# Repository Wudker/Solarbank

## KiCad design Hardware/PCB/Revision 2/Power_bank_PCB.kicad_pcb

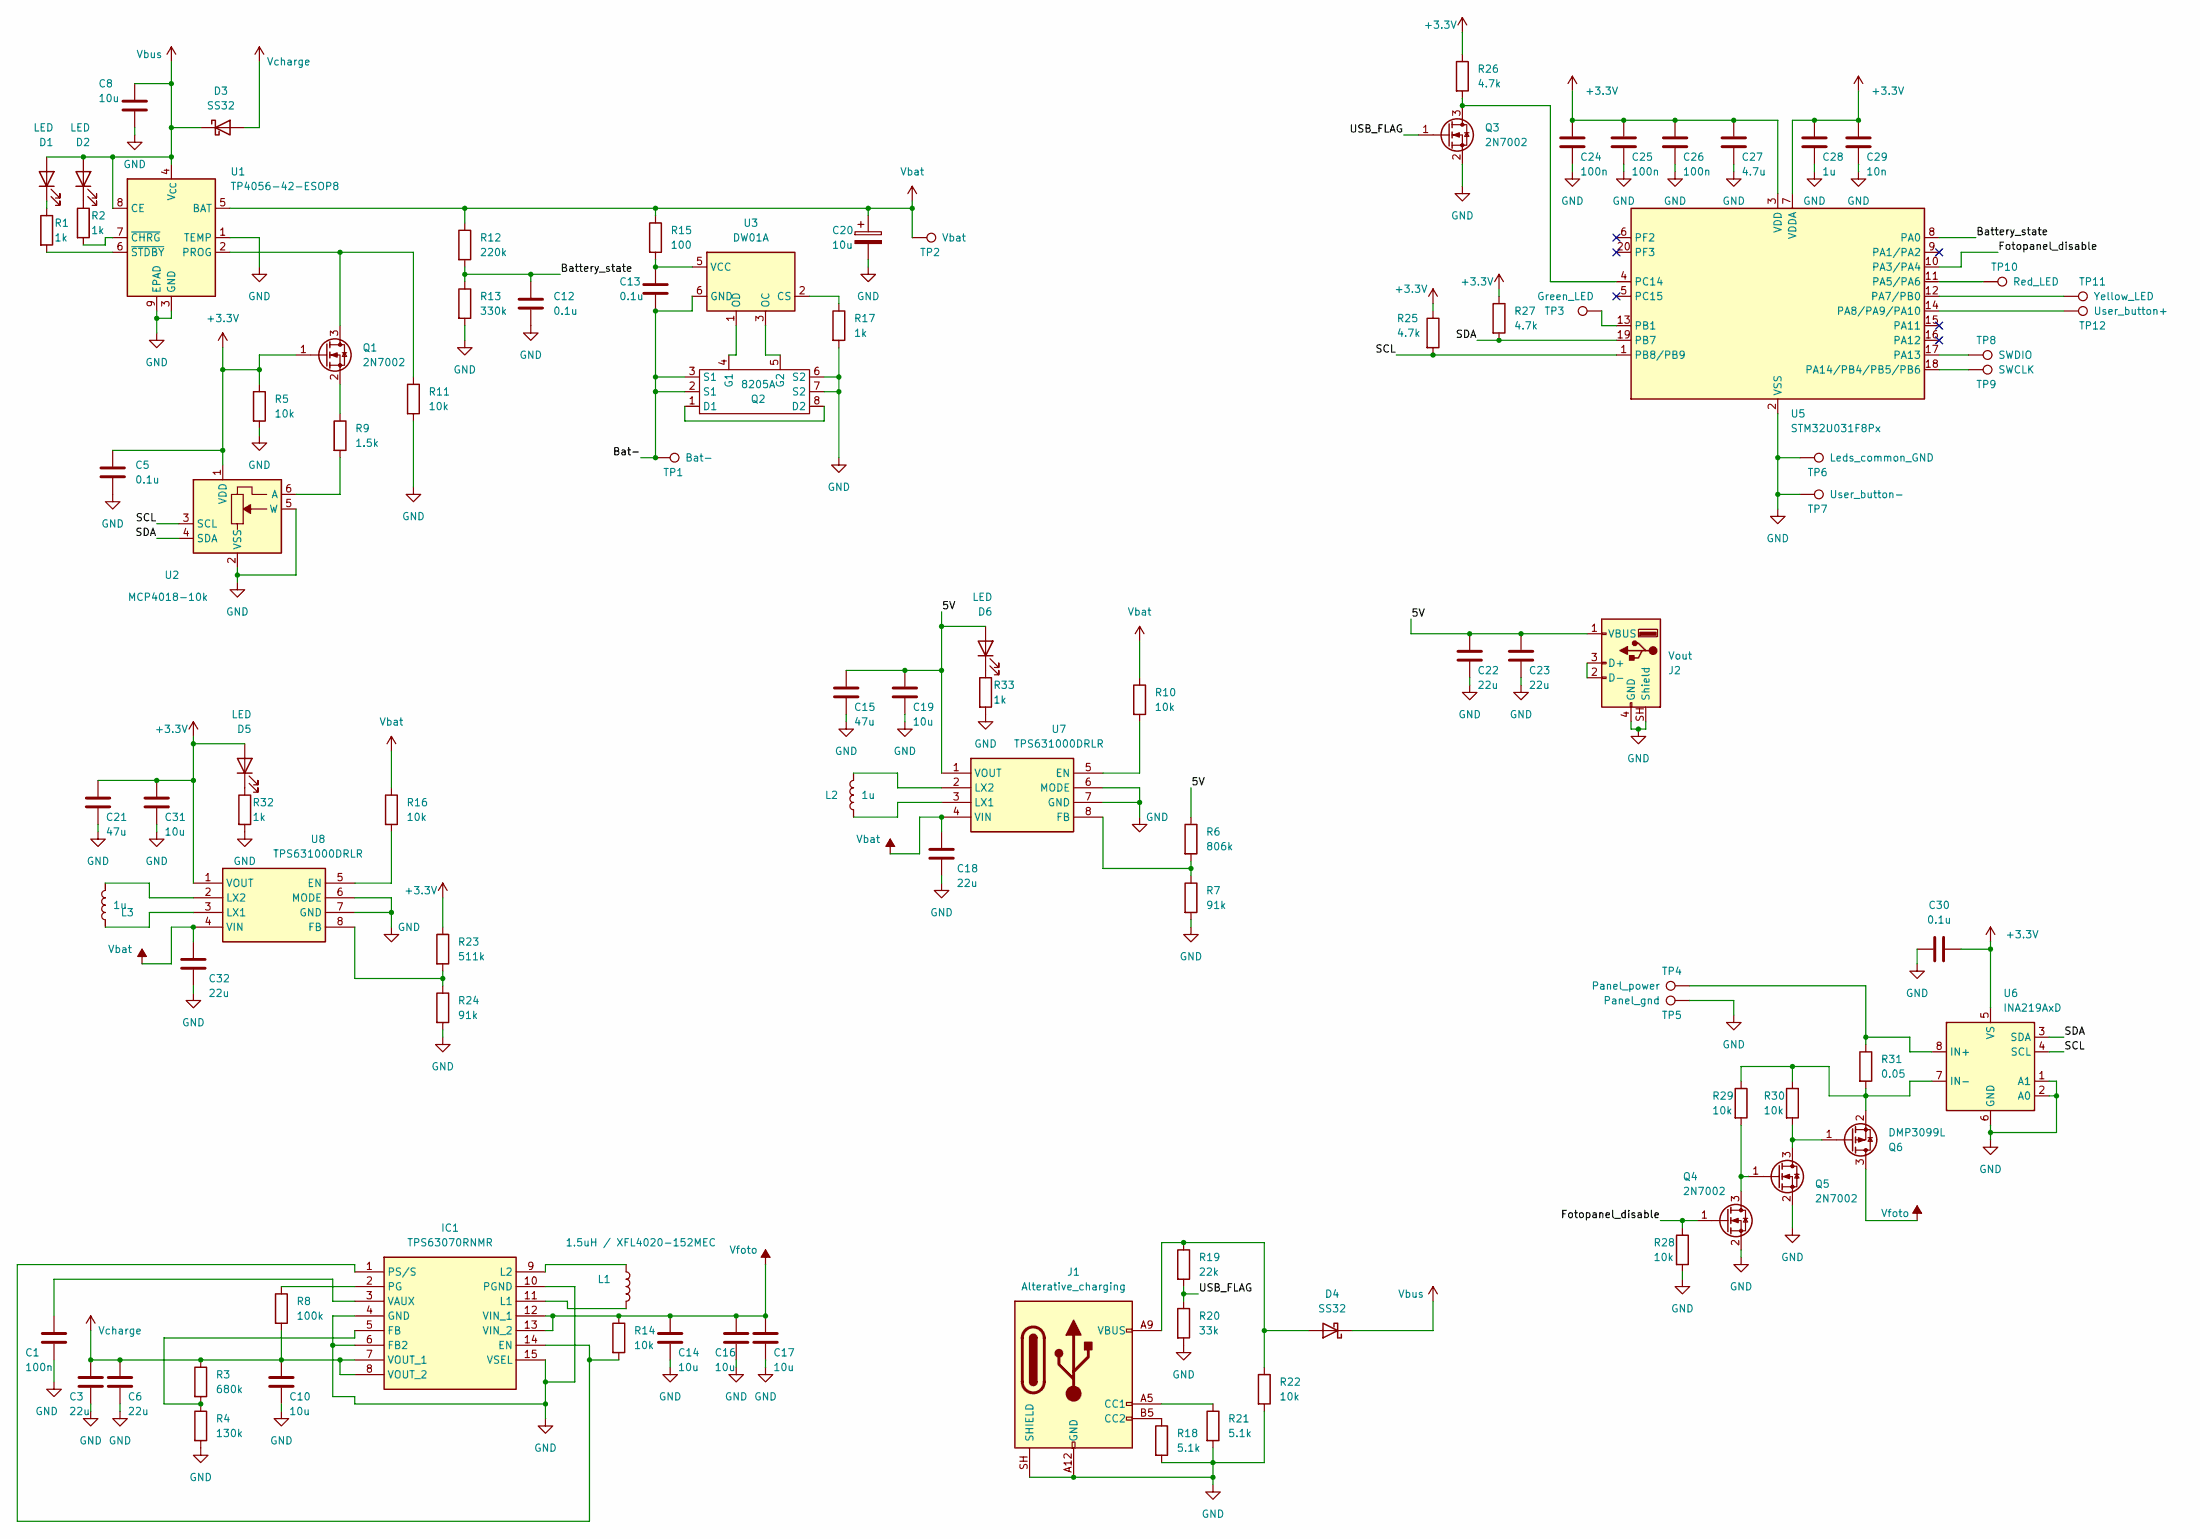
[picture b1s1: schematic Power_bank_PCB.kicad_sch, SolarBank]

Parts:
C1, C24, C25, C26: 100n; C_1206_3216Metric
C3, C6, C18, C22, C23, C32: 22u; C_1206_3216Metric
C5, C12, C13, C30: 0.1u; C_1206_3216Metric
C8, C10, C14, C16, C17, C19, C20, C31: 10u; C_1206_3216Metric
C15, C21: 47u; C_1206_3216Metric
C27: 4.7u; C_1206_3216Metric
C28: 1u; C_1206_3216Metric
C29: 10n; C_1206_3216Metric
D1, D2, D5, D6: LED; LED_1206_3216Metric_Pad1.42x1.75mm_HandSolder
D3, D4: SS32; D_SMA
IC1: TPS63070RNMR; TPS630701RNMR; Manufacturer_Part_Number TPS63070RNMR
J1: Alterative_charging; USB_C_Receptacle_GCT_USB4125-xx-x-0190_6P_TopMnt_Horizontal
J2: Vout; USB_A_Molex_67643_Horizontal
L1: 1.5uH / XFL4020-152MEC; L_Coilcraft_XAL4020-XXX
L2, L3: 1u; L_1008_2520Metric
Q1, Q3, Q4, Q5: 2N7002; SOT-23
Q2: 8205A; TSSOP-8_4.4x3mm_P0.65mm
Q6: DMP3099L; SOT-23
R1, R2, R17, R32, R33: 1k; R_1206_3216Metric
R3: 680k; R_1206_3216Metric
R4: 130k; R_1206_3216Metric
R5, R10, R11, R14, R16, R22, R28, R29, R30: 10k; R_1206_3216Metric
R6: 806k; R_1206_3216Metric
R7, R24: 91k; R_1206_3216Metric
R8: 100k; R_1206_3216Metric
R9: 1.5k; R_1206_3216Metric
R12: 220k; R_1206_3216Metric
R13: 330k; R_1206_3216Metric
R15: 100; R_1206_3216Metric
R18, R21: 5.1k; R_1206_3216Metric
R19: 22k; R_1206_3216Metric
R20: 33k; R_1206_3216Metric
R23: 511k; R_1206_3216Metric
R25, R26, R27: 4.7k; R_1206_3216Metric
R31: 0.05; R_1206_3216Metric
TP1: Bat-; TestPoint_Pad_D2.0mm
TP2: Vbat; TestPoint_Pad_D2.0mm
TP3: Green_LED; TestPoint_Pad_D2.0mm
TP4: Panel_power; TestPoint_Pad_D2.0mm
TP5: Panel_gnd; TestPoint_Pad_D2.0mm
TP6: Leds_common_GND; TestPoint_Pad_D2.0mm
TP7: User_button-; TestPoint_Pad_D2.0mm
TP8: SWDIO; TestPoint_Pad_D2.0mm
TP9: SWCLK; TestPoint_Pad_D2.0mm
TP10: Red_LED; TestPoint_Pad_D2.0mm
TP11: Yellow_LED; TestPoint_Pad_D2.0mm
TP12: User_button+; TestPoint_Pad_D2.0mm
U1: TP4056-42-ESOP8; SOIC-8-1EP_3.9x4.9mm_P1.27mm_EP2.41x3.3mm_ThermalVias
U2: MCP4018-10k; SOT-363_SC-70-6
U3: DW01A; SOT-23-6
U5: STM32U031F8Px; TSSOP-20_4.4x6.5mm_P0.65mm
U6: INA219AxD; SOIC-8_3.9x4.9mm_P1.27mm
U7, U8: TPS631000DRLR; SOT-583-8; Manufacturer_Part_Number TPS631000DRLR

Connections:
+3.3V: C5.1, C21.2, C24.2, C25.2, C26.2, C27.2, C28.2, C29.2, C30.2, C31.2, D5.2 (A), Q1.1 (G), R5.1, R23.1, R25.1, R26.1, R27.1, U2.1 (VDD), U5.3 (VDD), U5.7 (VDDA), U6.5 (VS), U8.1 (VOUT)
/5V: C15.2, C19.2, C22.2, C23.2, D6.2 (A), J2.1 (VBUS), R6.1, U7.1 (VOUT)
/Bat-: C13.1, Q2.2 (S1), Q2.3 (S1), TP1.1 (1_1), U3.6 (GND)
/Battery_state: C12.1, R12.2, R13.1, U5.8 (PA0)
/Fotopanel_disable: Q4.1 (G), R28.1, U5.10 (PA3/PA4)
/SCL: R25.2, U2.3 (SCL), U5.1 (PB8/PB9), U6.4 (SCL)
/SDA: R27.2, U2.4 (SDA), U5.19 (PB7), U6.3 (SDA)
/USB_FLAG: Q3.1 (G), R19.2, R20.1
GND: C1.1, C3.1, C5.2, C6.1, C8.2, C10.1, C12.2, C14.1, C15.1, C16.1, C17.1, C18.1, C19.1, C20.2, C21.1, C22.1, C23.1, C24.1, C25.1, C26.1, C27.1, C28.1, C29.1, C30.1, C31.1, C32.1, IC1.4 (GND), IC1.6 (FB2), IC1.10 (PGND), IC1.15 (VSEL), J1.A12 (GND), J1.B12 (GND), J1.SH (SHIELD), J2.4 (GND), J2.SH (Shield), Q2.6 (S2), Q2.7 (S2), Q3.2 (S), Q4.2 (S), Q5.2 (S), R4.2, R5.2, R7.2, R11.2, R13.2, R17.2, R18.2, R20.2, R21.2, R22.2, R24.2, R28.2, R32.2, R33.2, TP5.1 (1_1), TP6.1 (1_1), TP7.1 (1_1), U1.1 (TEMP), U1.3 (GND), U1.9 (EPAD), U2.2 (VSS), U2.5 (W), U5.2 (VSS), U6.1 (A1), U6.2 (A0), U6.6 (GND), U7.6 (MODE), U7.7 (GND), U8.6 (MODE), U8.7 (GND)
unnamed: D1.1 (K), R1.1
unnamed: D2.1 (K), R2.1
unnamed: D4.2 (A), J1.A9 (VBUS), J1.B9 (VBUS), R19.1, R22.1
unnamed: D5.1 (K), R32.1
unnamed: D6.1 (K), R33.1
unnamed: IC1.1 (PS/S), IC1.14 (EN), R14.2
unnamed: IC1.5 (FB), R3.2, R4.1
unnamed: IC1.11 (L1), L1.2
unnamed: IC1.9 (L2), L1.1
unnamed: IC1.2 (PG), R8.1
unnamed: C1.2, IC1.3 (VAUX)
unnamed: J1.A5 (CC1), R21.1
unnamed: J1.B5 (CC2), R18.1
unnamed: J2.2 (D-), J2.3 (D+)
unnamed: Q1.3 (D), R11.1, U1.2 (PROG)
unnamed: Q1.2 (S), R9.1
unnamed: Q2.1 (D1), Q2.8 (D2)
unnamed: Q2.4 (G1), U3.1 (OD)
unnamed: Q2.5 (G2), U3.3 (OC)
unnamed: Q3.3 (D), R26.2, U5.4 (PC14)
unnamed: Q4.3 (D), Q5.1 (G), R29.2
unnamed: Q5.3 (D), Q6.1 (G), R30.2
unnamed: Q6.2 (S), R29.1, R30.1, R31.2, U6.7 (IN-)
unnamed: R2.2, U1.7 (~CHRG)
unnamed: R1.2, U1.6 (~STDBY)
unnamed: R9.2, U2.6 (A)
unnamed: R17.1, U3.2 (CS)
unnamed: C13.2, R15.2, U3.5 (VCC)
unnamed: TP10.1 (1_1), U5.11 (PA5/PA6)
unnamed: TP11.1 (1_1), U5.12 (PA7/PB0)
unnamed: TP12.1 (1_1), U5.14 (PA8/PA9/PA10)
unnamed: TP8.1 (1_1), U5.17 (PA13)
unnamed: TP9.1 (1_1), U5.18 (PA14/PB4/PB5/PB6)
unnamed: TP3.1 (1_1), U5.13 (PB1)
unnamed: R31.1, TP4.1 (1_1), U6.8 (IN+)
unnamed: R10.2, U7.5 (EN)
unnamed: R6.2, R7.1, U7.8 (FB)
unnamed: L2.1, U7.3 (LX1)
unnamed: L2.2, U7.2 (LX2)
unnamed: R16.2, U8.5 (EN)
unnamed: R23.2, R24.1, U8.8 (FB)
unnamed: L3.1, U8.3 (LX1)
unnamed: L3.2, U8.2 (LX2)
Vbat: C18.2, C20.1, C32.2, R10.1, R12.1, R15.1, R16.1, TP2.1 (1_1), U1.5 (BAT), U7.4 (VIN), U8.4 (VIN)
Vbus: C8.1, D1.2 (A), D2.2 (A), D3.1 (K), D4.1 (K), U1.4 (V_{CC}), U1.8 (CE)
Vcharge: C3.2, C6.2, C10.2, D3.2 (A), IC1.7 (VOUT_1), IC1.8 (VOUT_2), R3.1, R8.2
Vfoto: C14.2, C16.2, C17.2, IC1.12 (VIN_1), IC1.13 (VIN_2), Q6.3 (D), R14.1

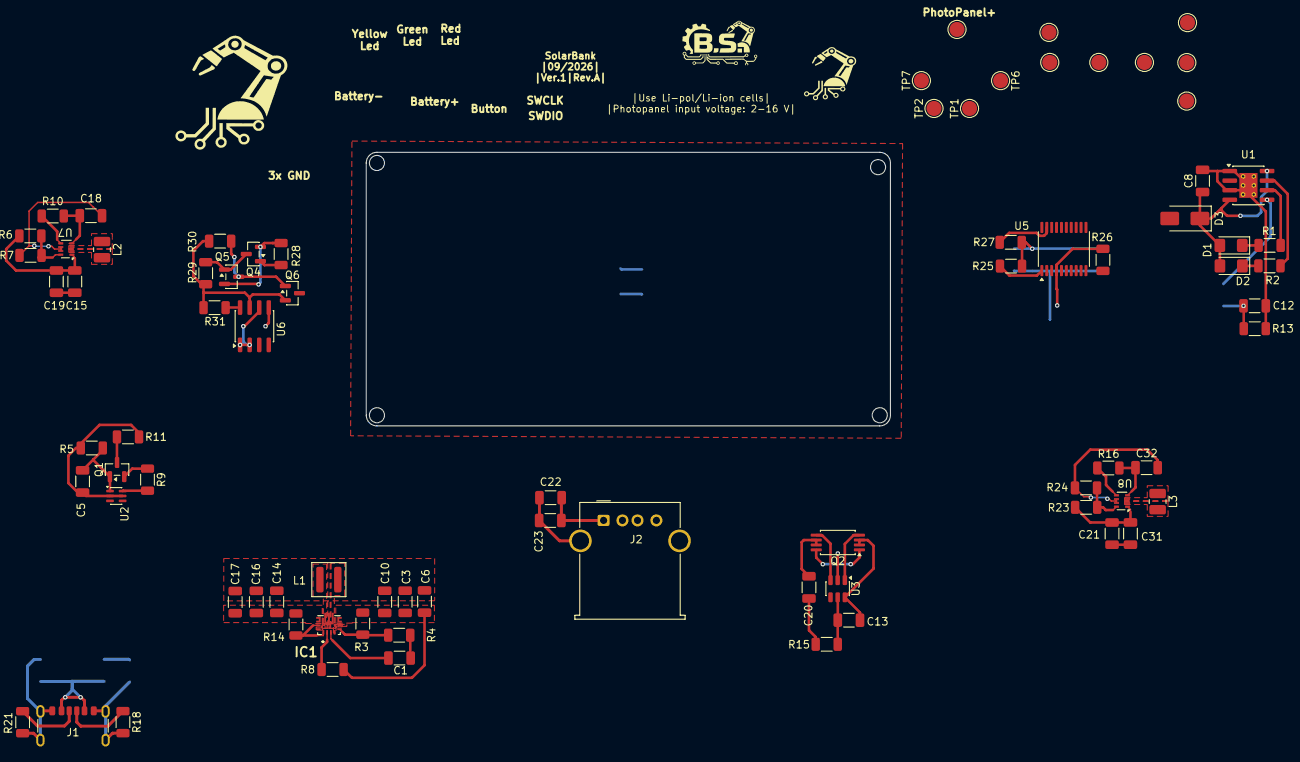
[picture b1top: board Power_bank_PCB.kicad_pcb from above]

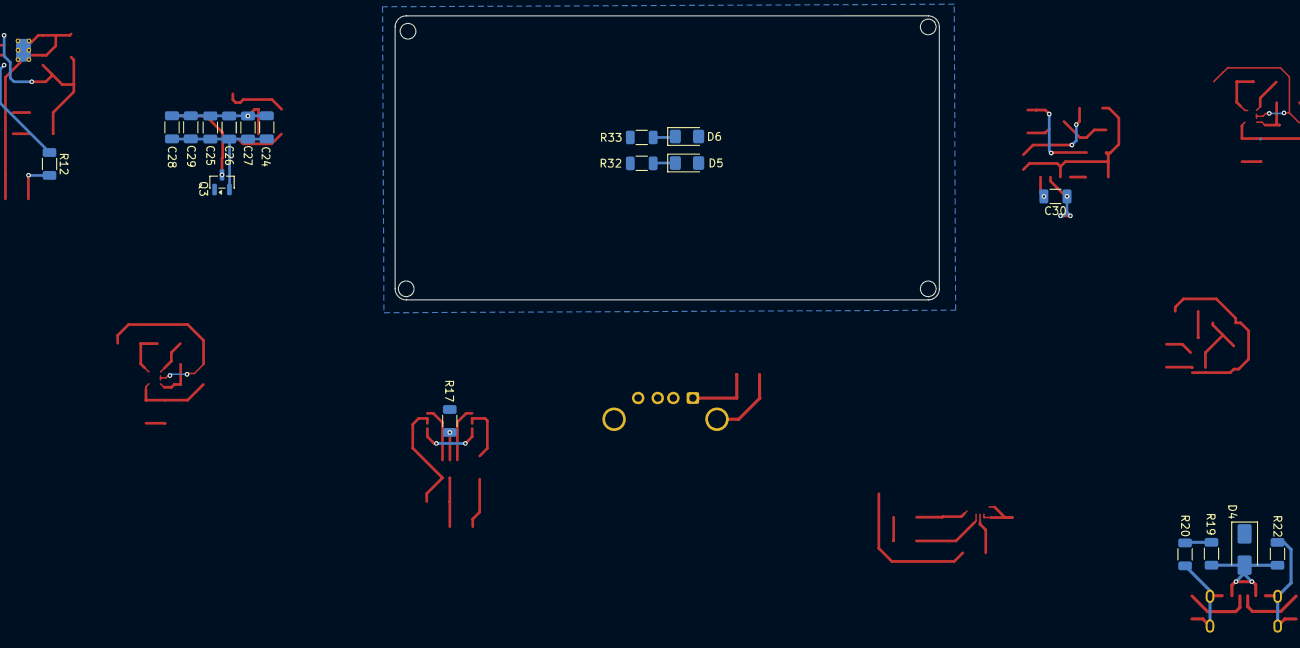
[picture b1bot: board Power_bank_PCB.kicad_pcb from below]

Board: 2 copper layers, 97 parts (18 on the bottom side), 56 nets.

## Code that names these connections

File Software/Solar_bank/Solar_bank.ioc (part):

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Mcu.Name=STM32U031F8Px
Mcu.Package=TSSOP20
Mcu.UserName=STM32U031F8Px
PA0-CK_IN.GPIOParameters=GPIO_Label
PA0-CK_IN.GPIO_Label=Battery_state
PA0-CK_IN.Mode=IN4
PA0-CK_IN.Signal=ADC1_IN4
PA13\ (SWDIO).Mode=Serial_Wire
PA13\ (SWDIO).Signal=DEBUG_JTMS-SWDIO
PA14\ (SWCLK).Mode=Serial_Wire
PA14\ (SWCLK).Signal=DEBUG_JTCK-SWCLK
PA14\ (SWCLK)__PB4__PB5__PB6.StandardMode=true
PA1__PA2.StandardMode=true
PA3.GPIOParameters=GPIO_Label
PA3.GPIO_Label=Fotopanel_enable
PA3.Signal=GPIO_Output
PA3__PA4.StandardMode=true
PA5__PA6.StandardMode=true
PA6.GPIOParameters=GPIO_Label
PA6.GPIO_Label=LED_status_red
PA6.Signal=GPIO_Output
PA7.GPIOParameters=GPIO_Label
PA7.GPIO_Label=LED_status_orange
PA7.Signal=GPIO_Output
PA7__PB0.StandardMode=true
PA8.GPIOParameters=GPIO_Label
PA8.GPIO_Label=User_button_input
PA8.Signal=GPXTI8
PB1.GPIOParameters=GPIO_Label
PB1.GPIO_Label=LED_status_green
PB1.Signal=GPIO_Output
PB7.Mode=I2C
PB7.Signal=I2C1_SDA
PB8.Mode=I2C
PB8.Signal=I2C1_SCL
PB8__PB9.StandardMode=true
PC14-OSC32_IN.GPIOParameters=GPIO_Label
PC14-OSC32_IN.GPIO_Label=USB_input
PC14-OSC32_IN.Signal=GPIO_Input
RCC.HSE_VALUE=4000000
RCC.SYSCLKFreq_VALUE=16000000
board=custom
